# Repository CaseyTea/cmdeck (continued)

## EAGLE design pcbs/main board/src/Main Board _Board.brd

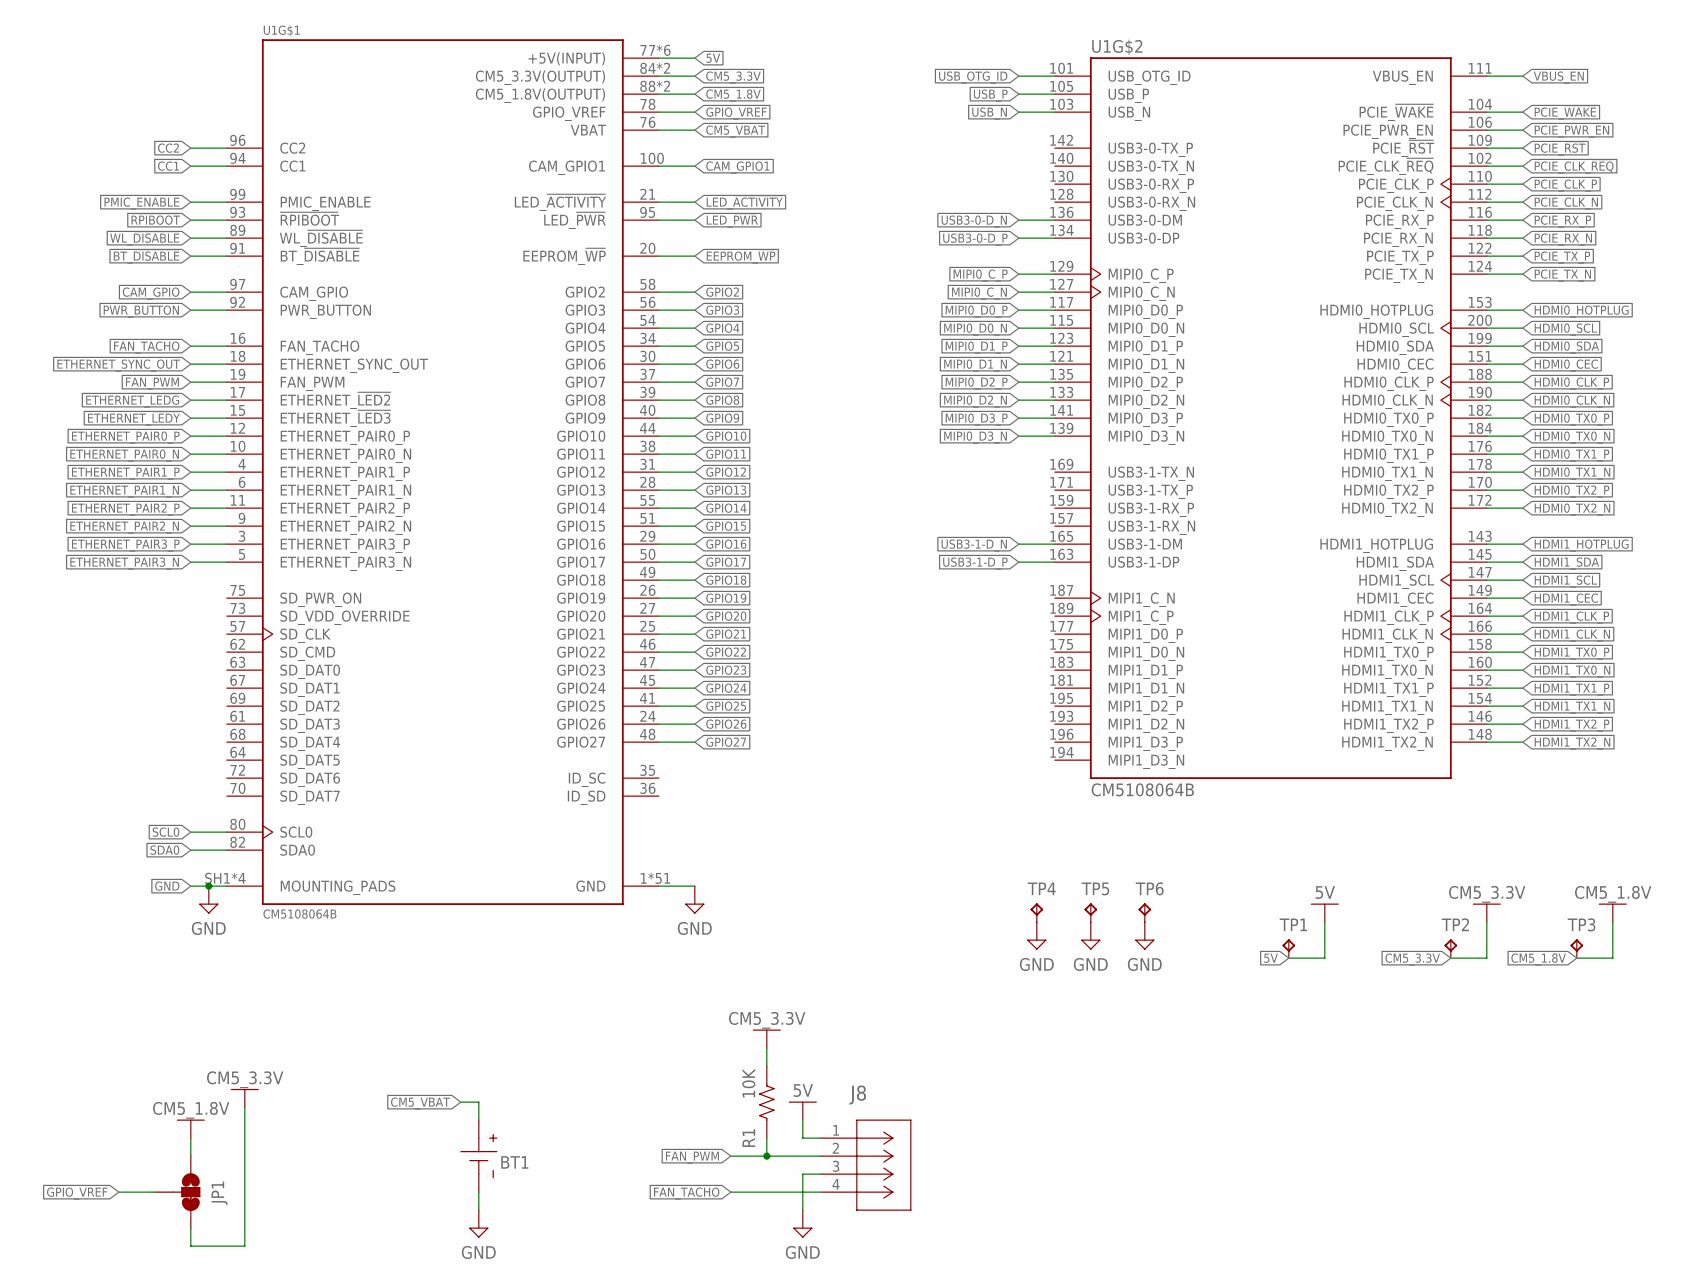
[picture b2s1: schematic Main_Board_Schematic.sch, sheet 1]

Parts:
BT1: COIN-CELL-SMT-3P-3002-BR2016; BAT_3002
J8: SM04B-SRSS-TBCONN_SM04B-SRSS-TB_JST; CONN_SM04B-SRSS-TB_JST
JP1: JUMPER-SMT_3_1-NC_TRACE_SILK; SMT-JUMPER_3_1-NC_TRACE_SILK
R1: 10K; RESC2012X65
TP1, TP2, TP3, TP4, TP5, TP6: TPB1,27; B1,27
U1: CM5108064B; MODULE_CM5108064B

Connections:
5V: J8.1, TP1.TP, U1.77 (+5V(INPUT)), U1.79 (+5V(INPUT)), U1.81 (+5V(INPUT)), U1.83 (+5V(INPUT)), U1.85 (+5V(INPUT)), U1.87 (+5V(INPUT)); also elsewhere on the board
!RPIBOOT: U1.93 (!RPIBOOT); also elsewhere on the board
BT_!DISABLE: U1.91 (BT_!DISABLE); also elsewhere on the board
CAM_GPIO: U1.97 (CAM_GPIO); also elsewhere on the board
CAM_GPIO1: U1.100 (CAM_GPIO1); also elsewhere on the board
CC1: U1.94 (CC1)
CC2: U1.96 (CC2)
CM5_1.8V: JP1.1, TP3.TP, U1.88 (CM5_1.8V(OUTPUT)), U1.90 (CM5_1.8V(OUTPUT))
CM5_3.3V: JP1.3, R1.2, TP2.TP, U1.84 (CM5_3.3V(OUTPUT)), U1.86 (CM5_3.3V(OUTPUT)); also elsewhere on the board
CM5_VBAT: BT1.P (+), BT1.P1 (+), U1.76 (VBAT)
EEPROM_!WP: U1.20 (EEPROM_!WP); also elsewhere on the board
ETHERNET_!LEDG: U1.17 (ETHERNET_!LED2); also elsewhere on the board
ETHERNET_!LEDY: U1.15 (ETHERNET_!LED3); also elsewhere on the board
ETHERNET_PAIR0_N: U1.10 (ETHERNET_PAIR0_N); also elsewhere on the board
ETHERNET_PAIR0_P: U1.12 (ETHERNET_PAIR0_P); also elsewhere on the board
ETHERNET_PAIR1_N: U1.6 (ETHERNET_PAIR1_N); also elsewhere on the board
ETHERNET_PAIR1_P: U1.4 (ETHERNET_PAIR1_P); also elsewhere on the board
ETHERNET_PAIR2_N: U1.9 (ETHERNET_PAIR2_N); also elsewhere on the board
ETHERNET_PAIR2_P: U1.11 (ETHERNET_PAIR2_P); also elsewhere on the board
ETHERNET_PAIR3_N: U1.5 (ETHERNET_PAIR3_N); also elsewhere on the board
ETHERNET_PAIR3_P: U1.3 (ETHERNET_PAIR3_P); also elsewhere on the board
ETHERNET_SYNC_OUT: U1.18 (ETHERNET_SYNC_OUT)
FAN_PWM: J8.2, R1.1, U1.19 (FAN_PWM)
FAN_TACHO: J8.4, U1.16 (FAN_TACHO)
GND: BT1.N (-), J8.3, TP4.TP, TP5.TP, TP6.TP, U1.1 (GND), U1.2 (GND), U1.7 (GND), U1.8 (GND), U1.13 (GND), U1.14 (GND), U1.22 (GND), U1.23 (GND), U1.32 (GND), U1.33 (GND), U1.42 (GND), U1.43 (GND), U1.52 (GND), U1.53 (GND), U1.59 (GND), U1.60 (GND), U1.65 (GND), U1.66 (GND), U1.71 (GND), U1.74 (GND), U1.98 (GND), U1.107 (GND), U1.108 (GND), U1.113 (GND), U1.114 (GND), U1.119 (GND), U1.120 (GND), U1.125 (GND), U1.126 (GND), U1.131 (GND), U1.132 (GND), U1.137 (GND), U1.138 (GND), U1.144 (GND), U1.150 (GND), U1.155 (GND), U1.156 (GND), U1.161 (GND), U1.162 (GND), U1.167 (GND), U1.168 (GND), U1.173 (GND), U1.174 (GND), U1.179 (GND), U1.180 (GND), U1.185 (GND), U1.186 (GND), U1.191 (GND), U1.192 (GND), U1.197 (GND), U1.198 (GND), U1.SH1 (MOUNTING_PADS), U1.SH2 (MOUNTING_PADS), U1.SH3 (MOUNTING_PADS), U1.SH4 (MOUNTING_PADS); also elsewhere on the board
GPIO2: U1.58 (GPIO2); also elsewhere on the board
GPIO3: U1.56 (GPIO3); also elsewhere on the board
GPIO4: U1.54 (GPIO4); also elsewhere on the board
GPIO5: U1.34 (GPIO5)
GPIO6: U1.30 (GPIO6); also elsewhere on the board
GPIO7: U1.37 (GPIO7); also elsewhere on the board
GPIO8: U1.39 (GPIO8); also elsewhere on the board
GPIO9: U1.40 (GPIO9); also elsewhere on the board
GPIO10: U1.44 (GPIO10); also elsewhere on the board
GPIO11: U1.38 (GPIO11); also elsewhere on the board
GPIO12: U1.31 (GPIO12)
GPIO13: U1.28 (GPIO13)
GPIO14: U1.55 (GPIO14); also elsewhere on the board
GPIO15: U1.51 (GPIO15); also elsewhere on the board
GPIO16: U1.29 (GPIO16); also elsewhere on the board
GPIO17: U1.50 (GPIO17); also elsewhere on the board
GPIO18: U1.49 (GPIO18); also elsewhere on the board
GPIO19: U1.26 (GPIO19); also elsewhere on the board
GPIO20: U1.27 (GPIO20)
GPIO21: U1.25 (GPIO21); also elsewhere on the board
GPIO22: U1.46 (GPIO22); also elsewhere on the board
GPIO23: U1.47 (GPIO23); also elsewhere on the board
GPIO24: U1.45 (GPIO24)
GPIO25: U1.41 (GPIO25)
GPIO26: U1.24 (GPIO26)
GPIO27: U1.48 (GPIO27); also elsewhere on the board
GPIO_VREF: JP1.2, U1.78 (GPIO_VREF)
HDMI0_CEC: U1.151 (HDMI0_CEC); also elsewhere on the board
HDMI0_CLK_N: U1.190 (HDMI0_CLK_N); also elsewhere on the board
HDMI0_CLK_P: U1.188 (HDMI0_CLK_P); also elsewhere on the board
HDMI0_HOTPLUG: U1.153 (HDMI0_HOTPLUG); also elsewhere on the board
HDMI0_SCL: U1.200 (HDMI0_SCL); also elsewhere on the board
HDMI0_SDA: U1.199 (HDMI0_SDA); also elsewhere on the board
HDMI0_TX0_N: U1.184 (HDMI0_TX0_N); also elsewhere on the board
HDMI0_TX0_P: U1.182 (HDMI0_TX0_P); also elsewhere on the board
HDMI0_TX1_N: U1.178 (HDMI0_TX1_N); also elsewhere on the board
HDMI0_TX1_P: U1.176 (HDMI0_TX1_P); also elsewhere on the board
HDMI0_TX2_N: U1.172 (HDMI0_TX2_N); also elsewhere on the board
HDMI0_TX2_P: U1.170 (HDMI0_TX2_P); also elsewhere on the board
HDMI1_CEC: U1.149 (HDMI1_CEC); also elsewhere on the board
HDMI1_CLK_N: U1.166 (HDMI1_CLK_N); also elsewhere on the board
HDMI1_CLK_P: U1.164 (HDMI1_CLK_P); also elsewhere on the board
HDMI1_HOTPLUG: U1.143 (HDMI1_HOTPLUG); also elsewhere on the board
HDMI1_SCL: U1.147 (HDMI1_SCL); also elsewhere on the board
HDMI1_SDA: U1.145 (HDMI1_SDA); also elsewhere on the board
HDMI1_TX0_N: U1.160 (HDMI1_TX0_N); also elsewhere on the board
HDMI1_TX0_P: U1.158 (HDMI1_TX0_P); also elsewhere on the board
HDMI1_TX1_N: U1.154 (HDMI1_TX1_N); also elsewhere on the board
HDMI1_TX1_P: U1.152 (HDMI1_TX1_P); also elsewhere on the board
HDMI1_TX2_N: U1.148 (HDMI1_TX2_N); also elsewhere on the board
HDMI1_TX2_P: U1.146 (HDMI1_TX2_P); also elsewhere on the board
LED_!ACTIVITY: U1.21 (LED_!ACTIVITY); also elsewhere on the board
LED_!PWR: U1.95 (LED_!PWR); also elsewhere on the board
MIPI0_C_N: U1.127 (MIPI0_C_N); also elsewhere on the board
MIPI0_C_P: U1.129 (MIPI0_C_P); also elsewhere on the board
MIPI0_D0_N: U1.115 (MIPI0_D0_N); also elsewhere on the board
MIPI0_D0_P: U1.117 (MIPI0_D0_P); also elsewhere on the board
MIPI0_D1_N: U1.121 (MIPI0_D1_N); also elsewhere on the board
MIPI0_D1_P: U1.123 (MIPI0_D1_P); also elsewhere on the board
MIPI0_D2_N: U1.133 (MIPI0_D2_N); also elsewhere on the board
MIPI0_D2_P: U1.135 (MIPI0_D2_P); also elsewhere on the board
MIPI0_D3_N: U1.139 (MIPI0_D3_N); also elsewhere on the board
MIPI0_D3_P: U1.141 (MIPI0_D3_P); also elsewhere on the board
PCIE_!RST: U1.109 (PCIE_!RST); also elsewhere on the board
PCIE_!WAKE: U1.104 (PCIE_!WAKE); also elsewhere on the board
PCIE_CLK_!REQ: U1.102 (PCIE_CLK_!REQ); also elsewhere on the board
PCIE_CLK_N: U1.112 (PCIE_CLK_N); also elsewhere on the board
PCIE_CLK_P: U1.110 (PCIE_CLK_P); also elsewhere on the board
PCIE_PWR_EN: U1.106 (PCIE_PWR_EN); also elsewhere on the board
PCIE_RX_N: U1.118 (PCIE_RX_N); also elsewhere on the board
PCIE_RX_P: U1.116 (PCIE_RX_P); also elsewhere on the board
PCIE_TX_N: U1.124 (PCIE_TX_N); also elsewhere on the board
PCIE_TX_P: U1.122 (PCIE_TX_P); also elsewhere on the board
PMIC_ENABLE: U1.99 (PMIC_ENABLE); also elsewhere on the board
PWR_BUTTON: U1.92 (PWR_BUTTON); also elsewhere on the board
SCL0: U1.80 (SCL0); also elsewhere on the board
SDA0: U1.82 (SDA0); also elsewhere on the board
USB3-0-D_N: U1.136 (USB3-0-DM)
USB3-0-D_P: U1.134 (USB3-0-DP)
USB3-1-D_N: U1.165 (USB3-1-DM); also elsewhere on the board
USB3-1-D_P: U1.163 (USB3-1-DP); also elsewhere on the board
USB_N: U1.103 (USB_N); also elsewhere on the board
USB_OTG_ID: U1.101 (USB_OTG_ID); also elsewhere on the board
USB_P: U1.105 (USB_P); also elsewhere on the board
VBUS_EN: U1.111 (VBUS_EN); also elsewhere on the board
WL_!DISABLE: U1.89 (WL_!DISABLE); also elsewhere on the board

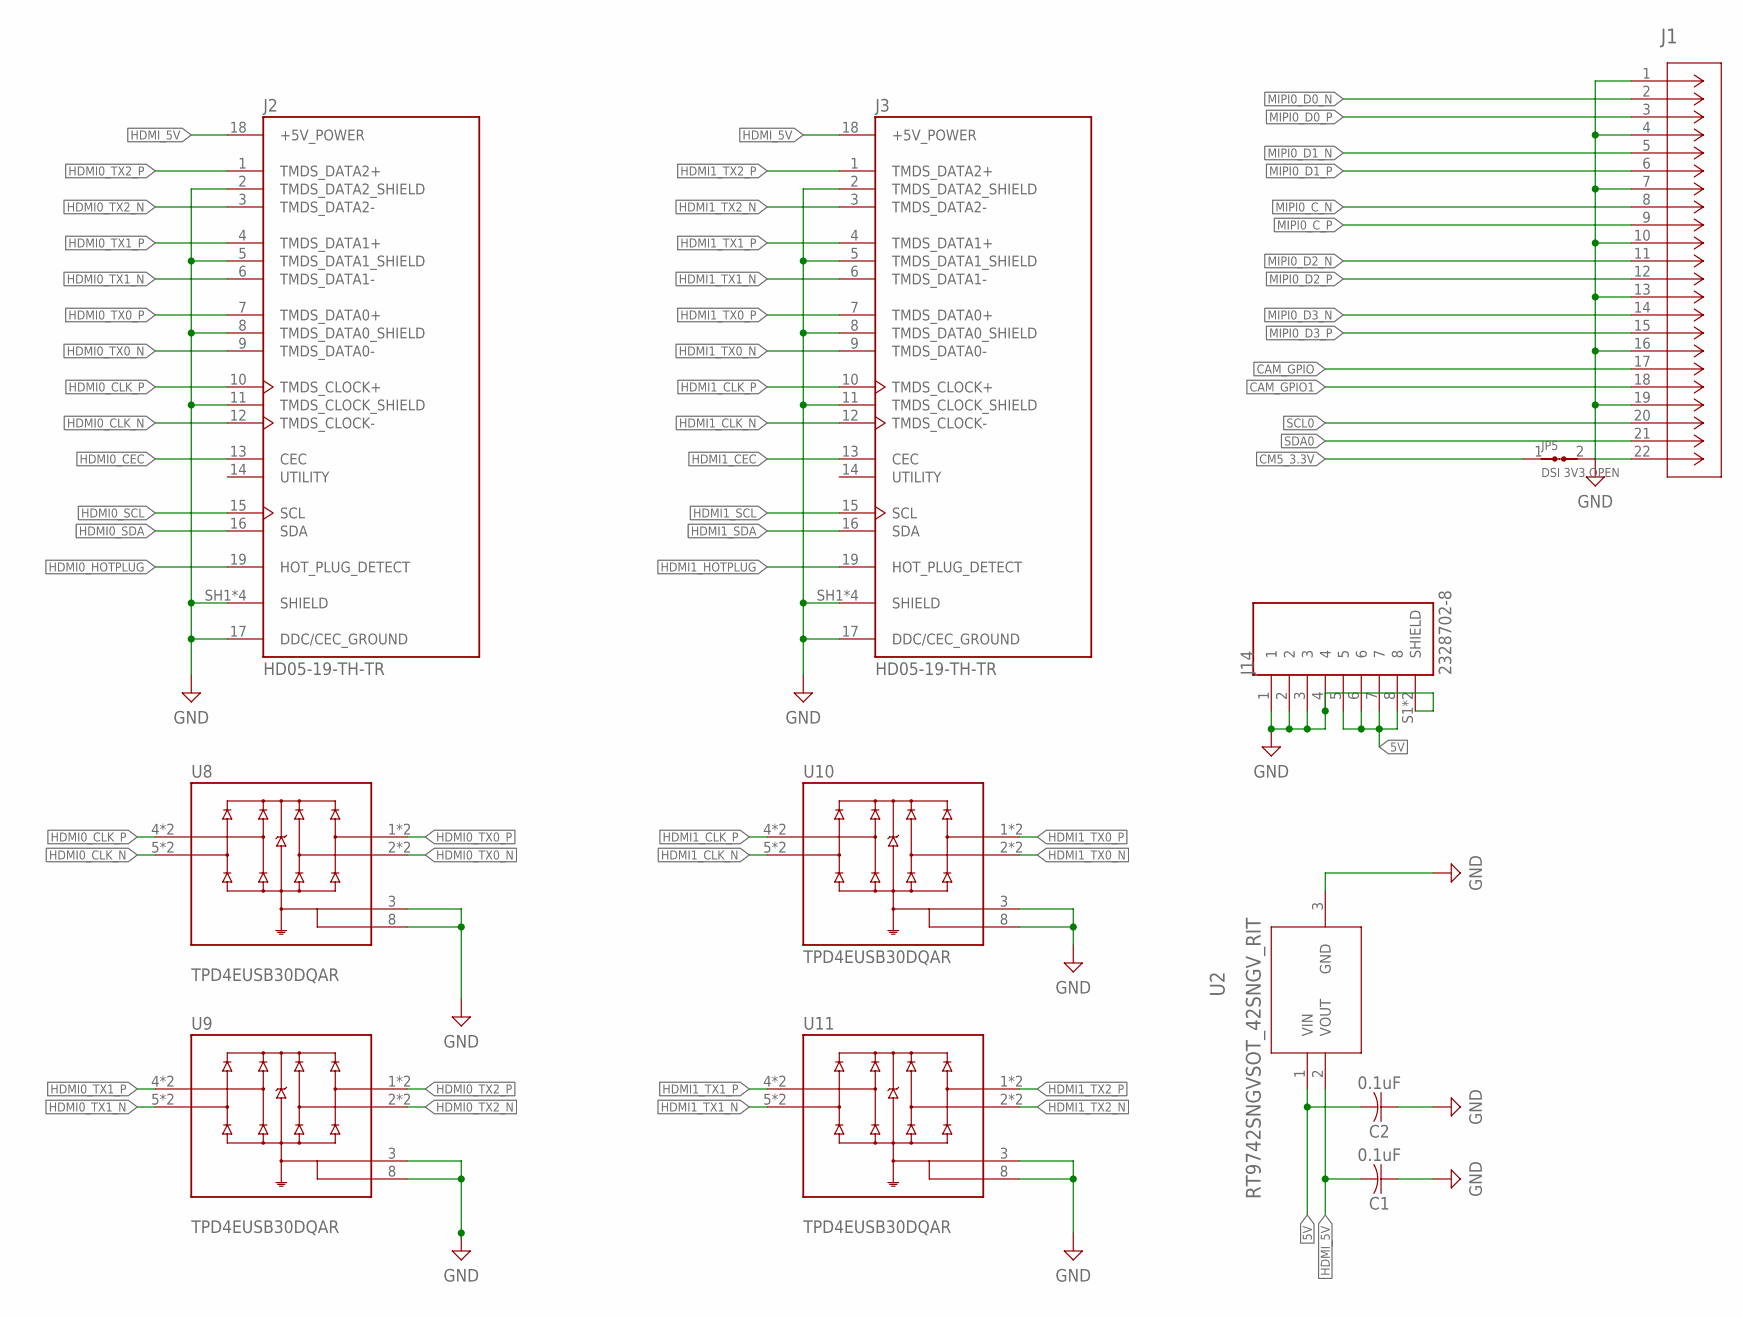
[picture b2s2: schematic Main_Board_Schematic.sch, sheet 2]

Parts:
C1, C2: 0.1uF; CAPC2012X110
J1: FH12-22S-0.5SH(55)CONN_FH12-22S-0.5SH(55)_HIR; CONN_FH12-22S-0.5SH(55)_HIR
J2, J3: HD05-19-TH-TR; SAMESKY_HD05-19-TH-TR
J14: 2328702-8; TE_2328702-8
JP5: DSI 3V3 OPEN; SJ_2_NO
U2: RT9742SNGVSOT_42SNGV_RIT; SOT_42SNGV_RIT
U8, U9, U10, U11: TPD4EUSB30DQAR; IC_TPD4EUSB30DQAR

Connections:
5V: C2.2, J14.5, J14.6, J14.7, J14.8, U2.1 (VIN); also elsewhere on the board
CAM_GPIO: J1.17; also elsewhere on the board
CAM_GPIO1: J1.18; also elsewhere on the board
CM5_3.3V: JP5.1; also elsewhere on the board
DSI_3V3: J1.22, JP5.2
GND: C1.1, C2.1, J1.1, J1.4, J1.7, J1.10, J1.13, J1.16, J1.19, J2.2 (TMDS_DATA2_SHIELD), J2.5 (TMDS_DATA1_SHIELD), J2.8 (TMDS_DATA0_SHIELD), J2.11 (TMDS_CLOCK_SHIELD), J2.17 (DDC/CEC_GROUND), J2.SH1 (SHIELD), J2.SH2 (SHIELD), J2.SH3 (SHIELD), J2.SH4 (SHIELD), J3.2 (TMDS_DATA2_SHIELD), J3.5 (TMDS_DATA1_SHIELD), J3.8 (TMDS_DATA0_SHIELD), J3.11 (TMDS_CLOCK_SHIELD), J3.17 (DDC/CEC_GROUND), J3.SH1 (SHIELD), J3.SH2 (SHIELD), J3.SH3 (SHIELD), J3.SH4 (SHIELD), J14.1, J14.2, J14.3, J14.4, J14.S1 (SHIELD), J14.S2 (SHIELD), U2.3 (GND), U8.3 (GND_3), U8.8 (GND_8), U9.3 (GND_3), U9.8 (GND_8), U10.3 (GND_3), U10.8 (GND_8), U11.3 (GND_3), U11.8 (GND_8); also elsewhere on the board
HDMI0_CEC: J2.13 (CEC); also elsewhere on the board
HDMI0_CLK_N: J2.12 (TMDS_CLOCK-), U8.5 (D2-), U8.6 (D2-); also elsewhere on the board
HDMI0_CLK_P: J2.10 (TMDS_CLOCK+), U8.4 (D2+), U8.7 (D2+); also elsewhere on the board
HDMI0_HOTPLUG: J2.19 (HOT_PLUG_DETECT); also elsewhere on the board
HDMI0_SCL: J2.15 (SCL); also elsewhere on the board
HDMI0_SDA: J2.16 (SDA); also elsewhere on the board
HDMI0_TX0_N: J2.9 (TMDS_DATA0-), U8.2 (D1-), U8.9 (D1-); also elsewhere on the board
HDMI0_TX0_P: J2.7 (TMDS_DATA0+), U8.1 (D1+), U8.10 (D1+); also elsewhere on the board
HDMI0_TX1_N: J2.6 (TMDS_DATA1-), U9.5 (D2-), U9.6 (D2-); also elsewhere on the board
HDMI0_TX1_P: J2.4 (TMDS_DATA1+), U9.4 (D2+), U9.7 (D2+); also elsewhere on the board
HDMI0_TX2_N: J2.3 (TMDS_DATA2-), U9.2 (D1-), U9.9 (D1-); also elsewhere on the board
HDMI0_TX2_P: J2.1 (TMDS_DATA2+), U9.1 (D1+), U9.10 (D1+); also elsewhere on the board
HDMI1_CEC: J3.13 (CEC); also elsewhere on the board
HDMI1_CLK_N: J3.12 (TMDS_CLOCK-), U10.5 (D2-), U10.6 (D2-); also elsewhere on the board
HDMI1_CLK_P: J3.10 (TMDS_CLOCK+), U10.4 (D2+), U10.7 (D2+); also elsewhere on the board
HDMI1_HOTPLUG: J3.19 (HOT_PLUG_DETECT); also elsewhere on the board
HDMI1_SCL: J3.15 (SCL); also elsewhere on the board
HDMI1_SDA: J3.16 (SDA); also elsewhere on the board
HDMI1_TX0_N: J3.9 (TMDS_DATA0-), U10.2 (D1-), U10.9 (D1-); also elsewhere on the board
HDMI1_TX0_P: J3.7 (TMDS_DATA0+), U10.1 (D1+), U10.10 (D1+); also elsewhere on the board
HDMI1_TX1_N: J3.6 (TMDS_DATA1-), U11.5 (D2-), U11.6 (D2-); also elsewhere on the board
HDMI1_TX1_P: J3.4 (TMDS_DATA1+), U11.4 (D2+), U11.7 (D2+); also elsewhere on the board
HDMI1_TX2_N: J3.3 (TMDS_DATA2-), U11.2 (D1-), U11.9 (D1-); also elsewhere on the board
HDMI1_TX2_P: J3.1 (TMDS_DATA2+), U11.1 (D1+), U11.10 (D1+); also elsewhere on the board
HDMI_5V: C1.2, J2.18 (+5V_POWER), J3.18 (+5V_POWER), U2.2 (VOUT)
MIPI0_C_N: J1.8; also elsewhere on the board
MIPI0_C_P: J1.9; also elsewhere on the board
MIPI0_D0_N: J1.2; also elsewhere on the board
MIPI0_D0_P: J1.3; also elsewhere on the board
MIPI0_D1_N: J1.5; also elsewhere on the board
MIPI0_D1_P: J1.6; also elsewhere on the board
MIPI0_D2_N: J1.11; also elsewhere on the board
MIPI0_D2_P: J1.12; also elsewhere on the board
MIPI0_D3_N: J1.14; also elsewhere on the board
MIPI0_D3_P: J1.15; also elsewhere on the board
SCL0: J1.20; also elsewhere on the board
SDA0: J1.21; also elsewhere on the board

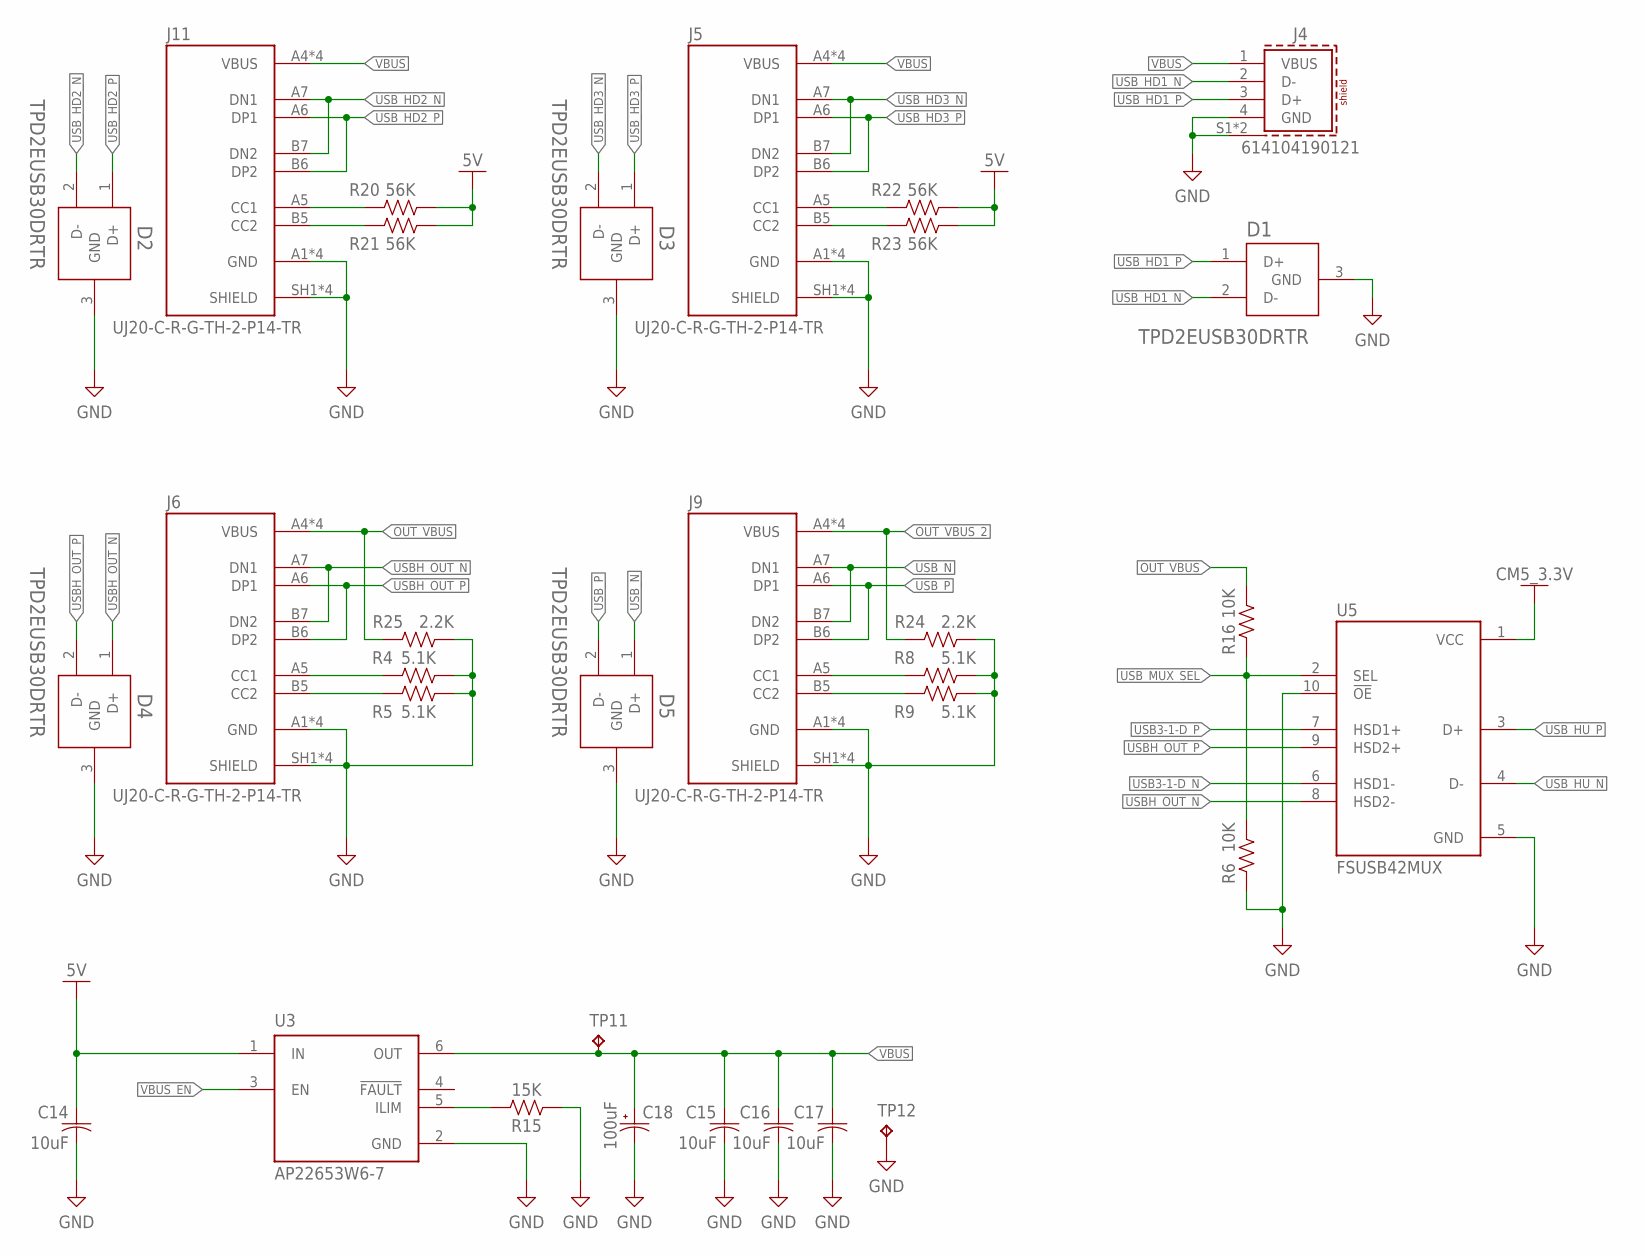
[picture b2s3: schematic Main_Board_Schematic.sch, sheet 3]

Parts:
C14, C15, C16, C17: 10uF; CAPC3216X135
C18: 100uF; CAPMP3528X210N
D1, D2, D3, D4, D5: TPD2EUSB30DRTR; SOTFL35P100X50-3N
J4: 614104190121
J5, J6, J9, J11: UJ20-C-R-G-TH-2-P14-TR; SAMESKY_UJ20-C-R-G-TH-2-P14-TR
R4, R5, R8, R9: 5.1K; RESC2012X65
R6, R16: 10K; RESC2012X65
R15: 15K; RESC2012X65
R20, R21, R22, R23: 56K; RESC2012X65
R24, R25: 2.2K; RESC2012X65
TP11, TP12: TPB1,27; B1,27
U3: AP22653W6-7; SOT95P280X145-6N
U5: FSUSB42MUX; SOP50P490X110-10N

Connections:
5V: C14.1, R20.1, R21.1, R22.1, R23.1, U3.1 (IN); also elsewhere on the board
CM5_3.3V: U5.1 (VCC); also elsewhere on the board
GND: C14.2, C15.2, C16.2, C17.2, C18.2 (-), D1.3 (GND), D2.3 (GND), D3.3 (GND), D4.3 (GND), D5.3 (GND), J4.4 (GND), J4.S1 (SHIELD), J4.S2 (SHIELD), J5.A1 (GND), J5.A12 (GND), J5.B1 (GND), J5.B12 (GND), J5.SH1 (SHIELD), J5.SH2 (SHIELD), J5.SH3 (SHIELD), J5.SH4 (SHIELD), J6.A1 (GND), J6.A12 (GND), J6.B1 (GND), J6.B12 (GND), J6.SH1 (SHIELD), J6.SH2 (SHIELD), J6.SH3 (SHIELD), J6.SH4 (SHIELD), J9.A1 (GND), J9.A12 (GND), J9.B1 (GND), J9.B12 (GND), J9.SH1 (SHIELD), J9.SH2 (SHIELD), J9.SH3 (SHIELD), J9.SH4 (SHIELD), J11.A1 (GND), J11.A12 (GND), J11.B1 (GND), J11.B12 (GND), J11.SH1 (SHIELD), J11.SH2 (SHIELD), J11.SH3 (SHIELD), J11.SH4 (SHIELD), R4.1, R5.1, R6.1, R8.1, R9.1, R15.1, R24.1, R25.1, TP12.TP, U3.2 (GND), U5.5 (GND), U5.10 (!OE); also elsewhere on the board
unnamed: J11.A5 (CC1), R20.2
unnamed: J5.A5 (CC1), R22.2
unnamed: J9.A5 (CC1), R8.2
unnamed: J9.B5 (CC2), R9.2
unnamed: J6.A5 (CC1), R4.2
unnamed: J6.B5 (CC2), R5.2
unnamed: R15.2, U3.5 (ILIM)
unnamed: J5.B5 (CC2), R23.2
unnamed: J11.B5 (CC2), R21.2
OUT_VBUS: J6.A4 (VBUS), J6.A9 (VBUS), J6.B4 (VBUS), J6.B9 (VBUS), R16.2, R25.2
OUT_VBUS_2: J9.A4 (VBUS), J9.A9 (VBUS), J9.B4 (VBUS), J9.B9 (VBUS), R24.2
USB3-1-D_N: U5.6 (HSD1-); also elsewhere on the board
USB3-1-D_P: U5.7 (HSD1+); also elsewhere on the board
USBH_OUT_N: D4.1 (D+), J6.A7 (DN1), J6.B7 (DN2), U5.8 (HSD2-)
USBH_OUT_P: D4.2 (D-), J6.A6 (DP1), J6.B6 (DP2), U5.9 (HSD2+)
USB_HD1_N: D1.2 (D-), J4.2 (D-); also elsewhere on the board
USB_HD1_P: D1.1 (D+), J4.3 (D+); also elsewhere on the board
USB_HD2_N: D2.2 (D-), J11.A7 (DN1), J11.B7 (DN2); also elsewhere on the board
USB_HD2_P: D2.1 (D+), J11.A6 (DP1), J11.B6 (DP2); also elsewhere on the board
USB_HD3_N: D3.2 (D-), J5.A7 (DN1), J5.B7 (DN2); also elsewhere on the board
USB_HD3_P: D3.1 (D+), J5.A6 (DP1), J5.B6 (DP2); also elsewhere on the board
USB_HU_N: U5.4 (D-); also elsewhere on the board
USB_HU_P: U5.3 (D+); also elsewhere on the board
USB_MUX_SEL: R6.2, R16.1, U5.2 (SEL)
USB_N: D5.1 (D+), J9.A7 (DN1), J9.B7 (DN2); also elsewhere on the board
USB_P: D5.2 (D-), J9.A6 (DP1), J9.B6 (DP2); also elsewhere on the board
VBUS: C15.1, C16.1, C17.1, C18.1 (+), J4.1 (VBUS), J5.A4 (VBUS), J5.A9 (VBUS), J5.B4 (VBUS), J5.B9 (VBUS), J11.A4 (VBUS), J11.A9 (VBUS), J11.B4 (VBUS), J11.B9 (VBUS), TP11.TP, U3.6 (OUT)
VBUS_EN: U3.3 (EN); also elsewhere on the board

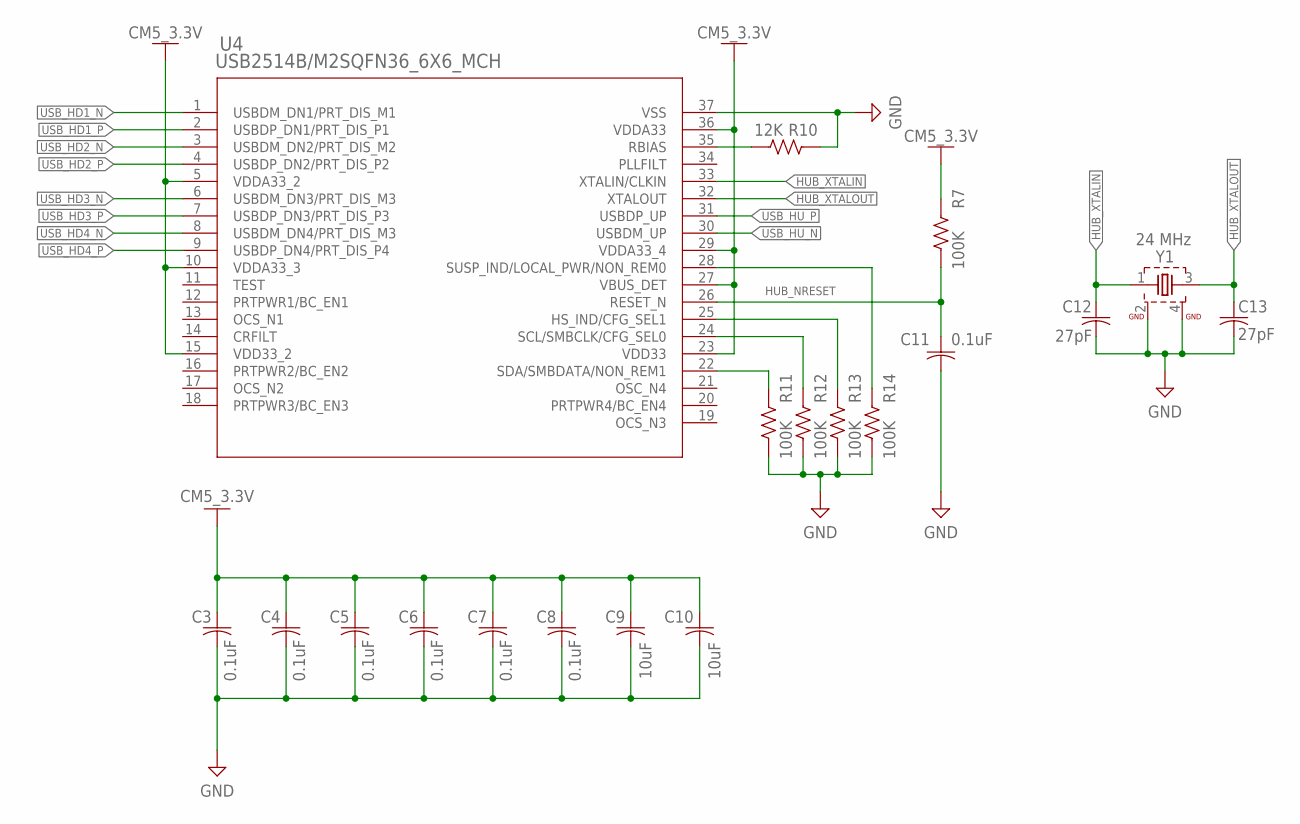
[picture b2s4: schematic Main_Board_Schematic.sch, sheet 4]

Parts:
C3, C4, C5, C6, C7, C8, C11: 0.1uF; CAPC2012X110
C9, C10: 10uF; CAPC3216X135
C12, C13: 27pF; CAPC2012X110
R7, R11, R12, R13, R14: 100K; RESC2012X65
R10: 12K; RESC2012X65
U4: USB2514B/M2SQFN36_6X6_MCH; SQFN36_6X6_MCH
Y1: 24 MHz; WE-XTAL_CFPX-180

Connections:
CM5_3.3V: C3.1, C4.1, C5.1, C6.1, C7.1, C8.1, C9.1, C10.1, R7.1, U4.5 (VDDA33_2), U4.10 (VDDA33_3), U4.15 (VDD33_2), U4.23 (VDD33), U4.27 (VBUS_DET), U4.29 (VDDA33_4), U4.36 (VDDA33); also elsewhere on the board
GND: C3.2, C4.2, C5.2, C6.2, C7.2, C8.2, C9.2, C10.2, C11.2, C12.2, C13.2, R10.1, R11.2, R12.2, R13.2, R14.2, U4.37 (VSS), Y1.2 (GND), Y1.4 (GND1); also elsewhere on the board
HUB_NRESET: C11.1, R7.2, U4.26 (RESET_N)
HUB_XTALIN: C12.1, U4.33 (XTALIN/CLKIN), Y1.1
HUB_XTALOUT: C13.1, U4.32 (XTALOUT), Y1.3 (2)
unnamed: R10.2, U4.35 (RBIAS)
unnamed: R11.1, U4.22 (SDA/SMBDATA/NON_REM1)
unnamed: R12.1, U4.24 (SCL/SMBCLK/CFG_SEL0)
unnamed: R13.1, U4.25 (HS_IND/CFG_SEL1)
unnamed: R14.1, U4.28 (SUSP_IND/LOCAL_PWR/NON_REM0)
USB_HD1_N: U4.1 (USBDM_DN1/PRT_DIS_M1); also elsewhere on the board
USB_HD1_P: U4.2 (USBDP_DN1/PRT_DIS_P1); also elsewhere on the board
USB_HD2_N: U4.3 (USBDM_DN2/PRT_DIS_M2); also elsewhere on the board
USB_HD2_P: U4.4 (USBDP_DN2/PRT_DIS_P2); also elsewhere on the board
USB_HD3_N: U4.6 (USBDM_DN3/PRT_DIS_M3); also elsewhere on the board
USB_HD3_P: U4.7 (USBDP_DN3/PRT_DIS_P3); also elsewhere on the board
USB_HD4_N: U4.8 (USBDM_DN4/PRT_DIS_M3); also elsewhere on the board
USB_HD4_P: U4.9 (USBDP_DN4/PRT_DIS_P4); also elsewhere on the board
USB_HU_N: U4.30 (USBDM_UP); also elsewhere on the board
USB_HU_P: U4.31 (USBDP_UP); also elsewhere on the board

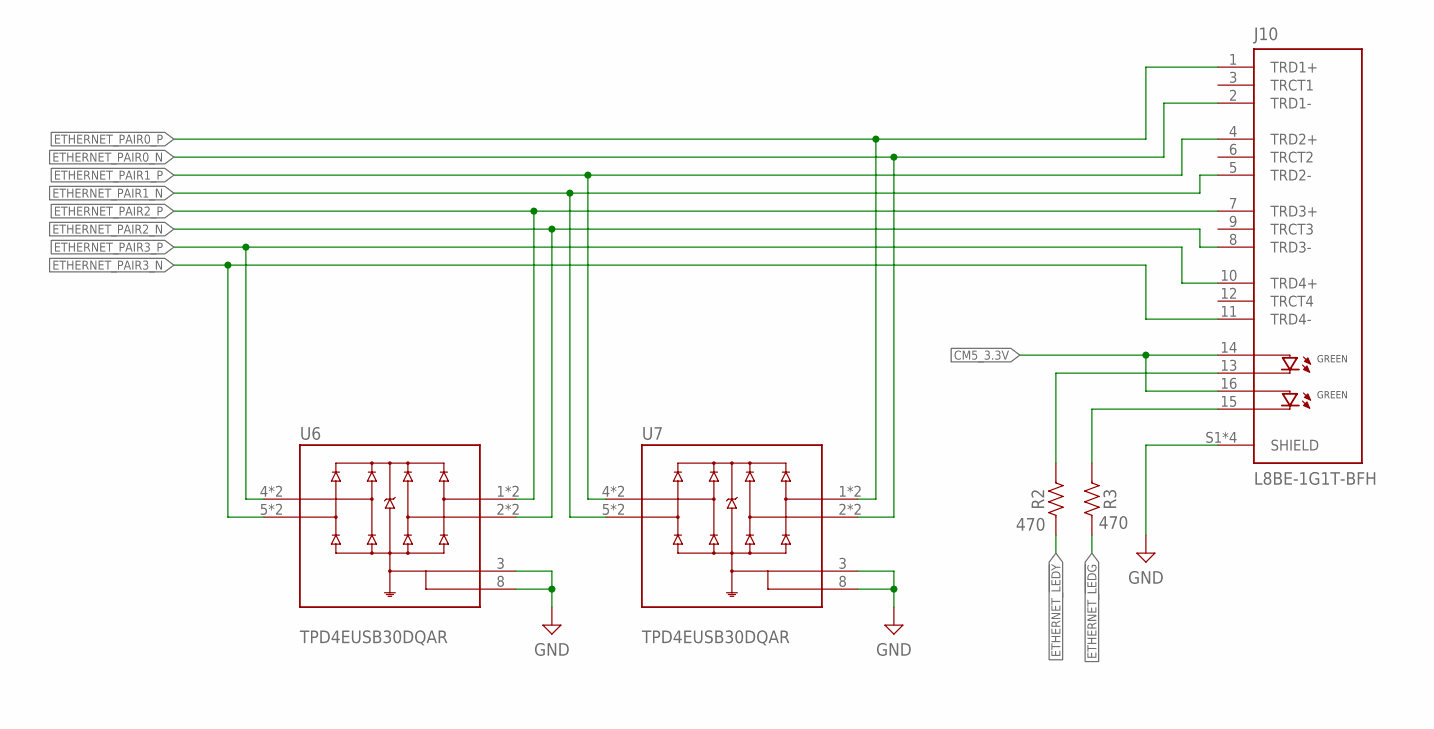
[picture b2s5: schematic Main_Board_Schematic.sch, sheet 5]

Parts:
J10: L8BE-1G1T-BFH; BEL_L8BE-1G1T-BFH
R2, R3: 470; RESC2012X65
U6, U7: TPD4EUSB30DQAR; IC_TPD4EUSB30DQAR

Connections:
CM5_3.3V: J10.14 (GA_1), J10.16 (GA_2); also elsewhere on the board
ETHERNET_!LEDG: R3.1; also elsewhere on the board
ETHERNET_!LEDY: R2.1; also elsewhere on the board
ETHERNET_PAIR0_N: J10.2 (TRD1-), U7.2 (D1-), U7.9 (D1-); also elsewhere on the board
ETHERNET_PAIR0_P: J10.1 (TRD1+), U7.1 (D1+), U7.10 (D1+); also elsewhere on the board
ETHERNET_PAIR1_N: J10.5 (TRD2-), U7.5 (D2-), U7.6 (D2-); also elsewhere on the board
ETHERNET_PAIR1_P: J10.4 (TRD2+), U7.4 (D2+), U7.7 (D2+); also elsewhere on the board
ETHERNET_PAIR2_N: J10.8 (TRD3-), U6.2 (D1-), U6.9 (D1-); also elsewhere on the board
ETHERNET_PAIR2_P: J10.7 (TRD3+), U6.1 (D1+), U6.10 (D1+); also elsewhere on the board
ETHERNET_PAIR3_N: J10.11 (TRD4-), U6.5 (D2-), U6.6 (D2-); also elsewhere on the board
ETHERNET_PAIR3_P: J10.10 (TRD4+), U6.4 (D2+), U6.7 (D2+); also elsewhere on the board
GND: J10.S1 (SHIELD), J10.S2 (SHIELD), J10.S3 (SHIELD), J10.S4 (SHIELD), U6.3 (GND_3), U6.8 (GND_8), U7.3 (GND_3), U7.8 (GND_8); also elsewhere on the board
unnamed: J10.15 (GK_2), R3.2
unnamed: J10.13 (GK_1), R2.2

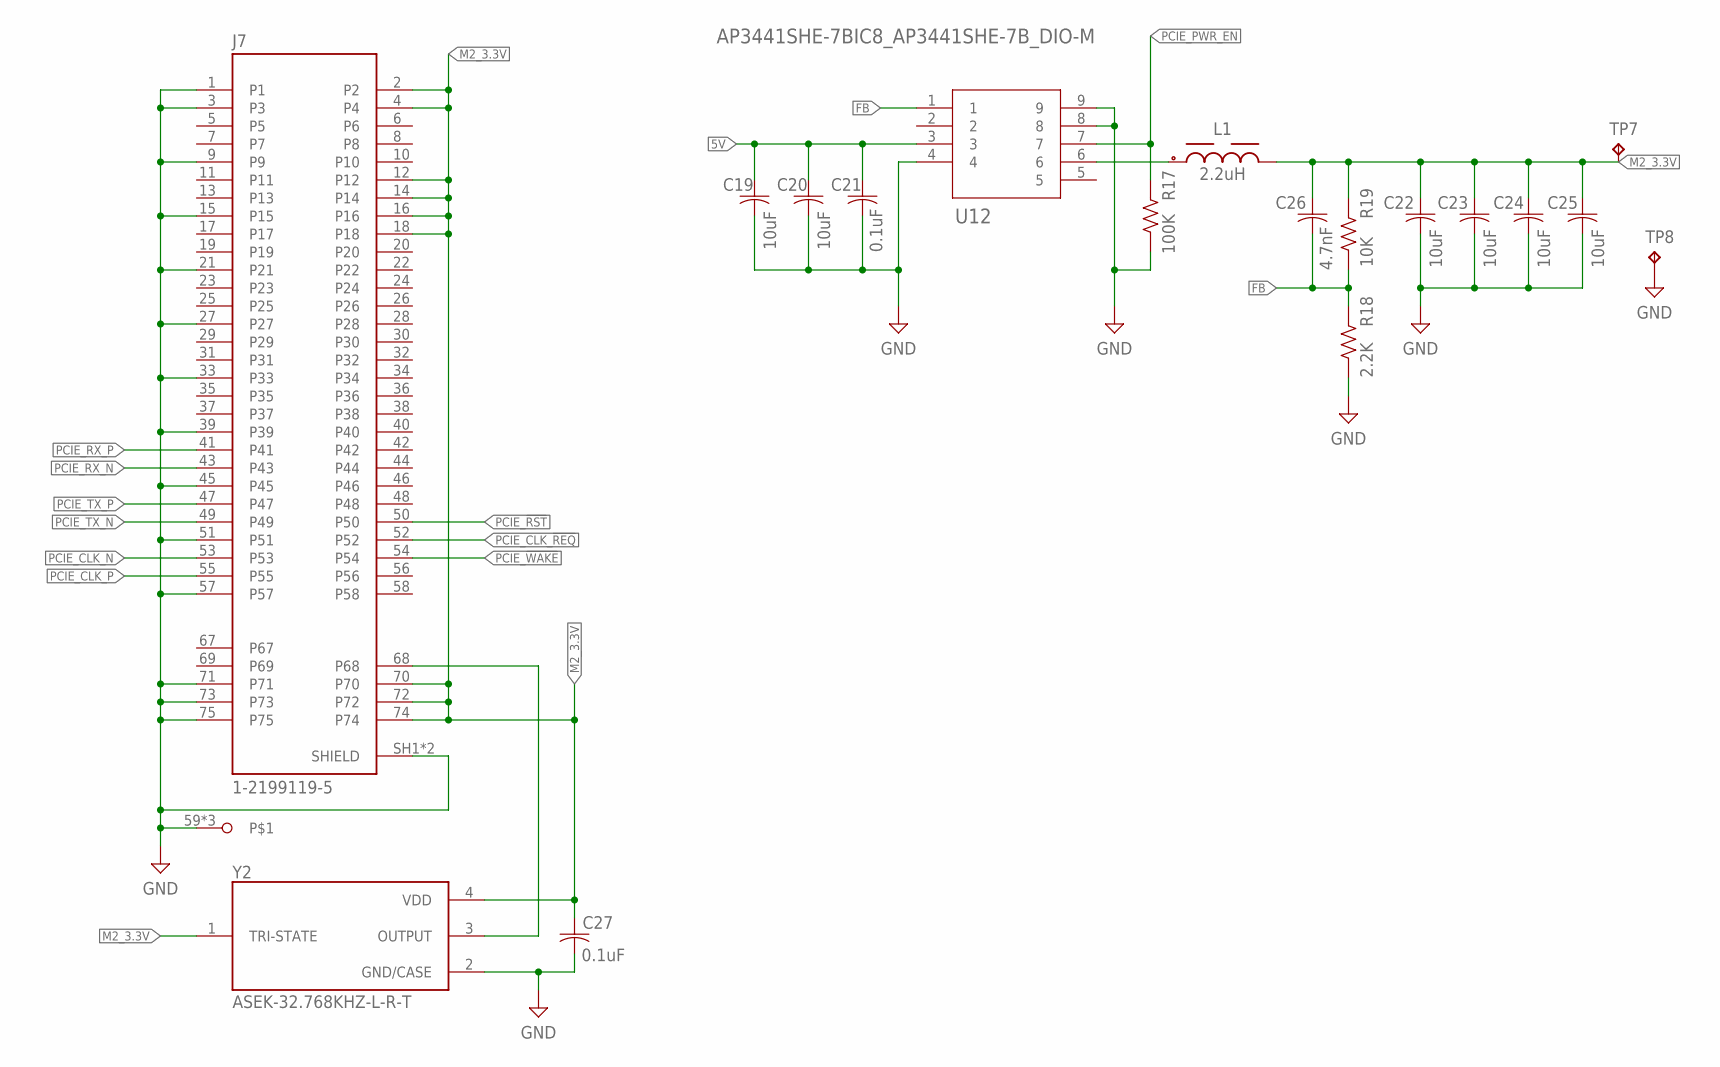
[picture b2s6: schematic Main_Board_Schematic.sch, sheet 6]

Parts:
C19, C20, C22, C23, C24, C25: 10uF; CAPC3216X135
C21, C27: 0.1uF; CAPC2012X110
C26: 4.7nF; CAPC2012X110
J7: 1-2199119-5; TE_1-2199119-5
L1: 2.2uH; WE-XHMI_5030
R17: 100K; RESC2012X65
R18: 2.2K; RESC2012X65
R19: 10K; RESC2012X65
TP7, TP8: TPB1,27; B1,27
U12: AP3441SHE-7BIC8_AP3441SHE-7B_DIO-M; IC8_AP3441SHE-7B_DIO-M
Y2: ASEK-32.768KHZ-L-R-T; XTAL_ASEK-32.768KHZ-L-R-T

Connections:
5V: C19.1, C20.1, C21.1, U12.3; also elsewhere on the board
FB: C26.2, R18.1, R19.2, U12.1
GND: C19.2, C20.2, C21.2, C22.2, C23.2, C24.2, C25.2, C27.2, J7.1, J7.3, J7.9, J7.15, J7.21, J7.27, J7.33, J7.39, J7.45, J7.51, J7.57, J7.59, J7.60, J7.61, J7.71, J7.73, J7.75, J7.SH1 (SHIELD), J7.SH2 (SHIELD), R17.2, R18.2, TP8.TP, U12.4, U12.8, U12.9, Y2.2 (GND/CASE); also elsewhere on the board
M2_3.3V: C22.1, C23.1, C24.1, C25.1, C26.1, C27.1, J7.2, J7.4, J7.12, J7.14, J7.16, J7.18, J7.70, J7.72, J7.74, L1.2, R19.1, TP7.TP, Y2.1 (TRI-STATE), Y2.4 (VDD)
unnamed: L1.1, U12.6
unnamed: J7.68, Y2.3 (OUTPUT)
PCIE_!RST: J7.50; also elsewhere on the board
PCIE_!WAKE: J7.54; also elsewhere on the board
PCIE_CLK_!REQ: J7.52; also elsewhere on the board
PCIE_CLK_N: J7.53; also elsewhere on the board
PCIE_CLK_P: J7.55; also elsewhere on the board
PCIE_PWR_EN: R17.1, U12.7; also elsewhere on the board
PCIE_RX_N: J7.43; also elsewhere on the board
PCIE_RX_P: J7.41; also elsewhere on the board
PCIE_TX_N: J7.49; also elsewhere on the board
PCIE_TX_P: J7.47; also elsewhere on the board
